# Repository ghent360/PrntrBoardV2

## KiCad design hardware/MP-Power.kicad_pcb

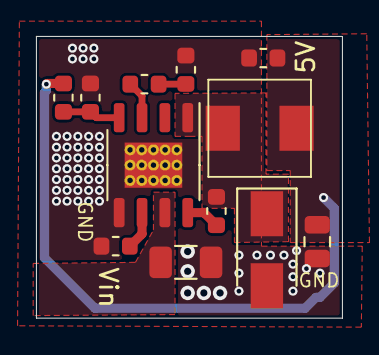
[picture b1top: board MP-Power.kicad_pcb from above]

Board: 2 copper layers, 17.0 x 15.7 mm, 12 parts (0 on the bottom side), 9 nets.

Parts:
C1: 10uF 50V; C_1206_3216Metric
C2, C5: 0.1uF; C_0603_1608Metric
C3: 150pF; C_0603_1608Metric
C4: 22uF; C_0805_2012Metric
D1: SS34; D_SMA
L1: 10uH; MWSA0503
R1, R2: 100k; R_0603_1608Metric
R3: 210k; R_0603_1608Metric
R4: 40.2k; R_0603_1608Metric
U1: MP1584EN; SOIC-8-1EP_3.9x4.9mm_P1.27mm_EP2.514x3.2mm_ThermalVias

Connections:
/5V: C4.1, C5.1, L1.2, R3.1
/Vin: C1.1, U1.7
GND: C1.2, C4.2, C5.2, D1.2, R1.2, R2.2, R4.2, U1.5, U1.9
unnamed: C2.1, D1.1, L1.1, U1.1
unnamed: C2.2, U1.8
unnamed: C3.1, U1.3
unnamed: C3.2, R2.1
unnamed: R1.1, U1.6
unnamed: R3.2, R4.1, U1.4

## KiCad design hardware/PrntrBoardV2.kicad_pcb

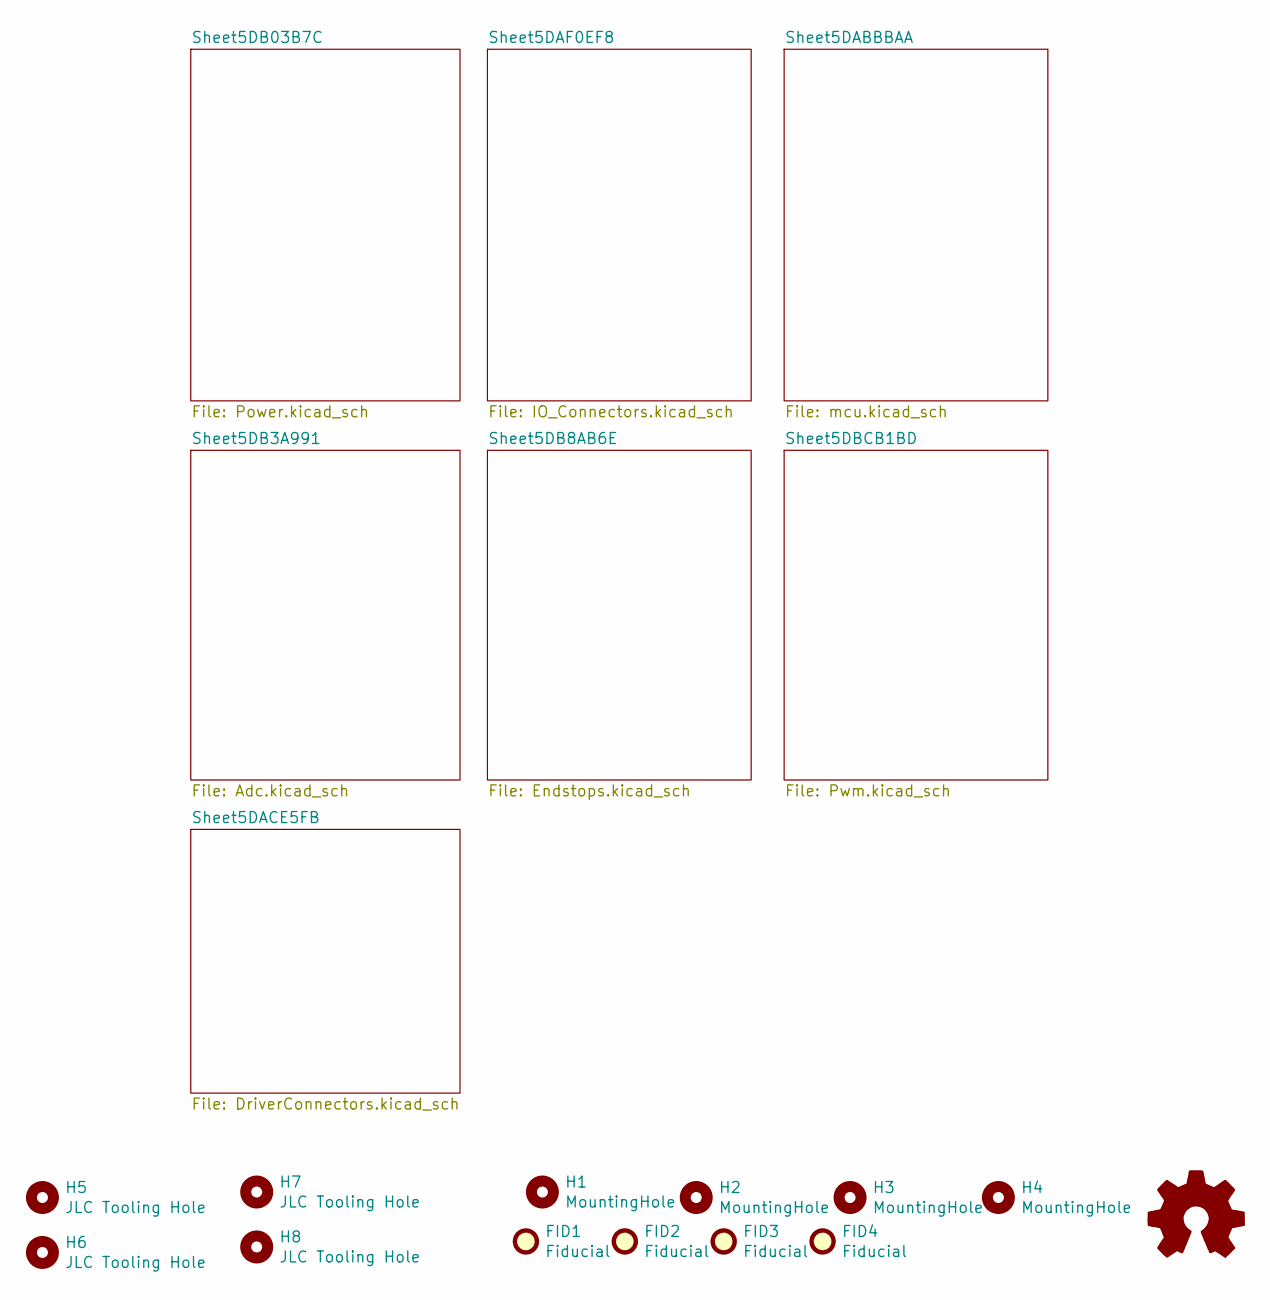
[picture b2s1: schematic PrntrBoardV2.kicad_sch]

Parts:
FID1, FID2, FID3, FID4: Fiducial; Fiducial_1mm_Dia_2.54mm_Outer_CopperTop
H1, H2, H3, H4: MountingHole; MountingHole_3.2mm_M3
H5, H6, H7, H8: JLC Tooling Hole; JLC_Tool_hole
LOGO1: Logo_Open_Hardware_Small; OSHW-Logo2_9.8x8mm_SilkScreen

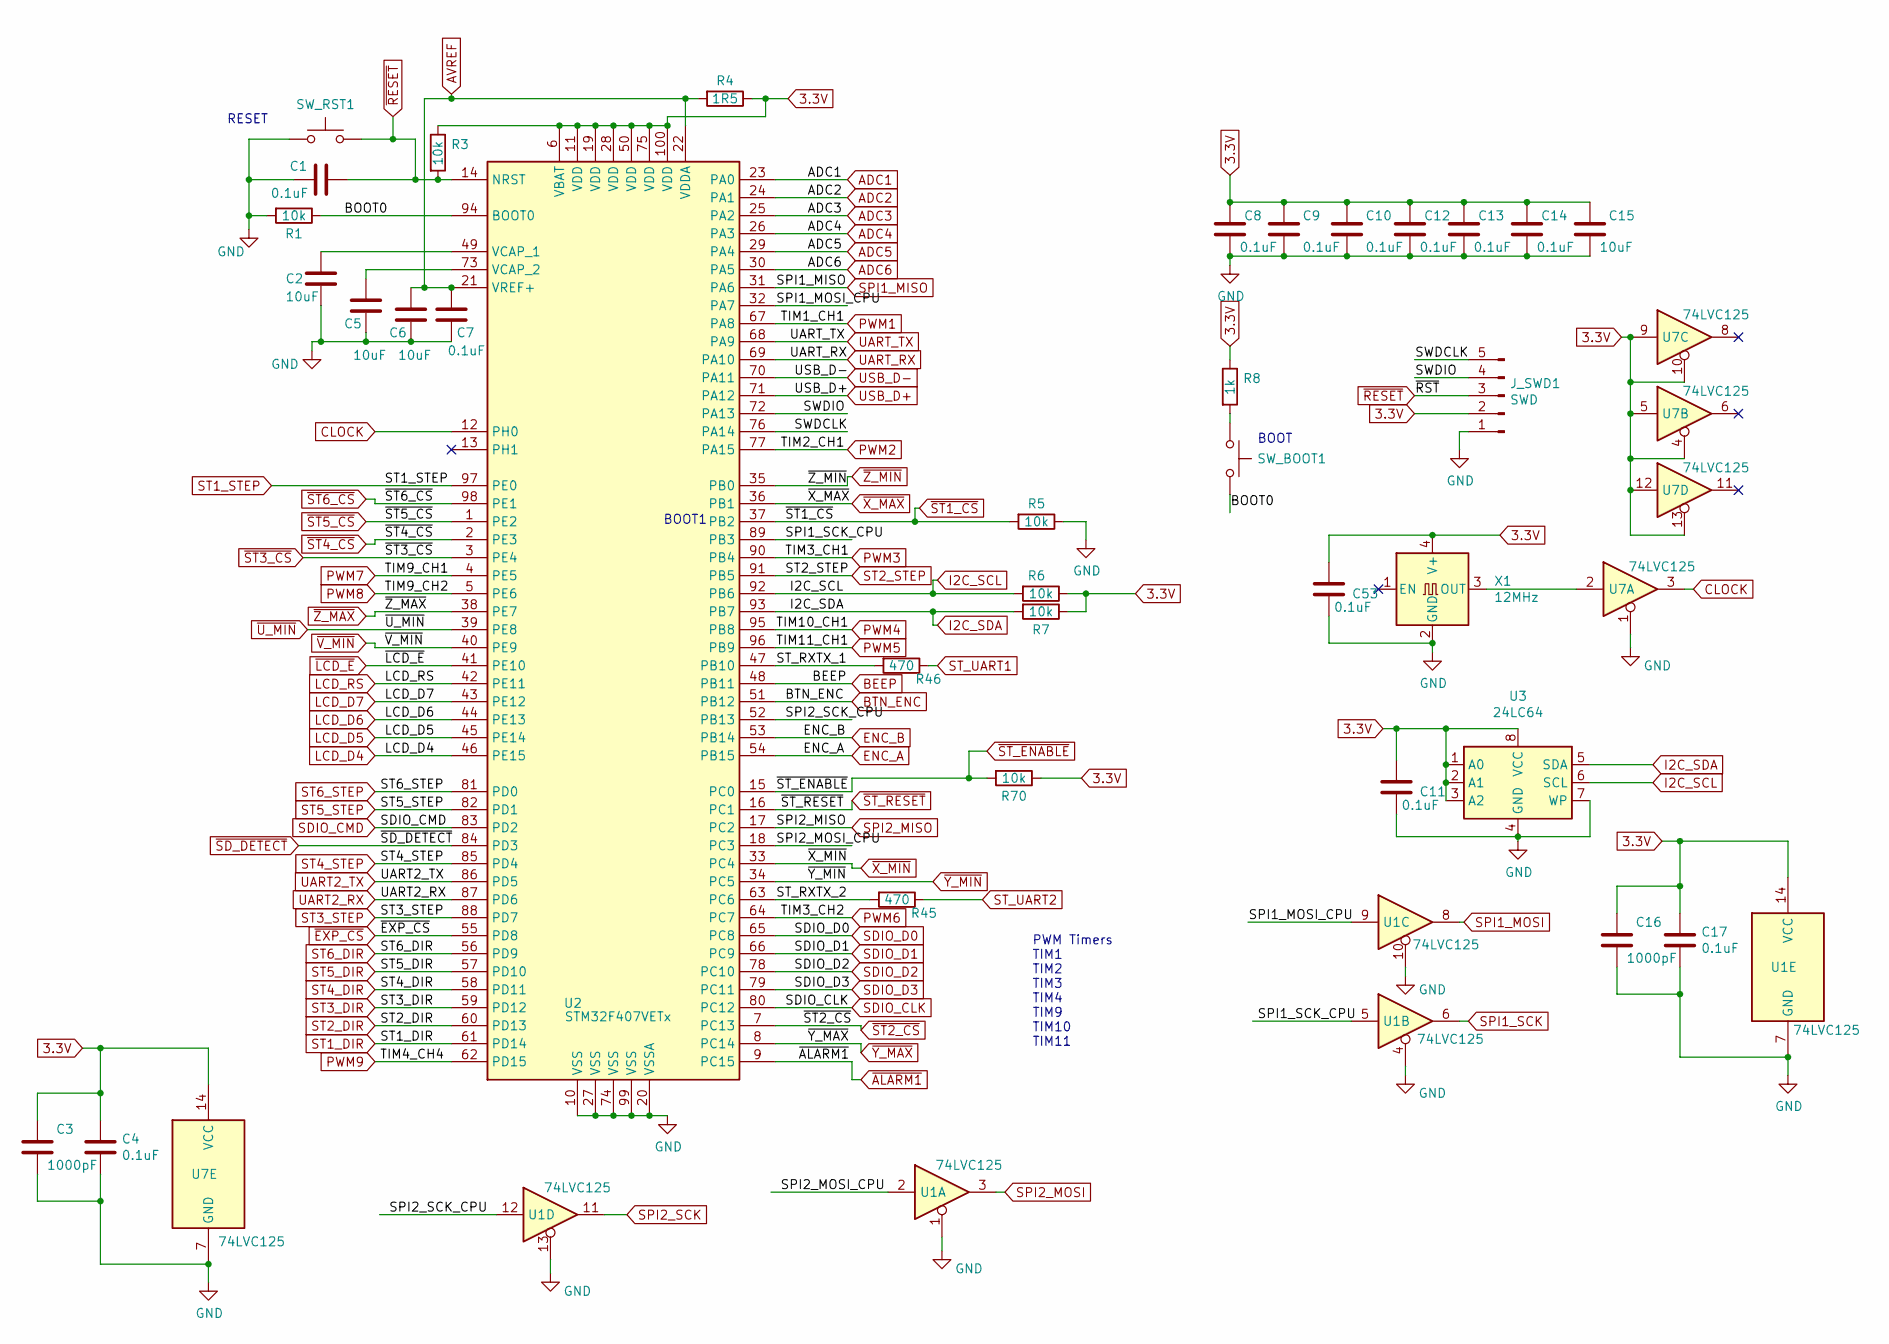
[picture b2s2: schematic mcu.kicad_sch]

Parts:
C1, C4, C7, C8, C9, C10, C11, C12, C13, C14, C17, C53: 0.1uF; C_0603_1608Metric; Part # CC0603KRX7R9BB104; LCSC Part # C14663
C2, C5, C6, C15: 10uF; C_0603_1608Metric; Part # CL10A106KP8NNNC; LCSC Part # C19702
C3, C16: 1000pF; C_0603_1608Metric; Part # CL10B102KB8NNNC; LCSC Part # C1588
J_SWD1: SWD; PinHeader_1x05_P2.54mm_Vertical
R1, R3, R5, R6, R7, R70: 10k; R_0603_1608Metric; Part # 0603WAF1002T5E; LCSC Part # C25804
R4: 1R5; R_0603_1608Metric; Part # 0603WAF220KT5E; LCSC Part # C22939
R8: 1k; R_0603_1608Metric; Part # 0603WAF1001T5E; LCSC Part # C21190
R45, R46: 470; R_0603_1608Metric; Part # 0603WAF4700T5E; LCSC Part # C23179
SW_BOOT1: SW_Push; Button_4x4; Part # TS-1187A-B-A-B; LCSC Part # C318884
SW_RST1: SW_Push; Button_4x4; Part # TS-1187A-B-A-B; LCSC Part # C318884
U1, U7: 74LVC125; TSSOP-14_4.4x5mm_P0.65mm; Part # 74LVC125APW,118; LCSC Part # C6059
U2: STM32F407VETx; LQFP-100_14x14mm_P0.5mm; Part # STM32F407VET6; LCSC Part # C28730
U3: 24LC64; SO-8_3.9x4.9mm_P1.27mm; Part # 24LC64T-I/SN; LCSC Part # C5460
X1: 12MHz; Oscillator_SMD_EuroQuartz_XO32-4Pin_3.2x2.5mm; Part# SIT1602AI-22-33E-12.000000D; LCSC Part # C29752

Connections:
3.3V: C3.1, C4.1, C8.1, C9.1, C10.1, C11.1, C12.1, C13.1, C14.1, C15.1, C16.1, C17.1, C53.1, J_SWD1.2, R3.1, R4.1, R6.1, R7.1, R8.1, R70.1, U1.14 (VCC), U2.6 (VBAT), U2.11 (VDD), U2.19 (VDD), U2.28 (VDD), U2.50 (VDD), U2.75 (VDD), U2.100 (VDD), U3.1 (A0), U3.2 (A1), U3.3 (A2), U3.8 (VCC), U7.4, U7.5, U7.9, U7.10, U7.12, U7.13, U7.14 (VCC), X1.4 (V+); also elsewhere on the board
/Sheet5DABBBAA/BOOT0: R1.1, SW_BOOT1.2, U2.94 (BOOT0)
/Sheet5DABBBAA/SPI1_MOSI_CPU: U1.9, U2.32 (PA7)
/Sheet5DABBBAA/SPI1_SCK_CPU: U1.5, U2.89 (PB3)
/Sheet5DABBBAA/SPI2_MOSI_CPU: U1.2, U2.18 (PC3)
/Sheet5DABBBAA/SPI2_SCK_CPU: U1.12, U2.52 (PB13)
/Sheet5DABBBAA/ST_RXTX_1: R46.2, U2.47 (PB10)
/Sheet5DABBBAA/ST_RXTX_2: R45.2, U2.63 (PC6)
/Sheet5DABBBAA/SWDCLK: J_SWD1.5, U2.76 (PA14)
/Sheet5DABBBAA/SWDIO: J_SWD1.4, U2.72 (PA13)
ADC1: U2.23 (PA0); also elsewhere on the board
ADC2: U2.24 (PA1); also elsewhere on the board
ADC3: U2.25 (PA2); also elsewhere on the board
ADC4: U2.26 (PA3); also elsewhere on the board
ADC5: U2.29 (PA4); also elsewhere on the board
ADC6: U2.30 (PA5); also elsewhere on the board
AVREF: C6.1, C7.1, R4.2, U2.21 (VREF+), U2.22 (VDDA); also elsewhere on the board
BEEP: U2.48 (PB11); also elsewhere on the board
BTN_ENC: U2.51 (PB12); also elsewhere on the board
CLOCK: U2.12 (PH0), U7.3; also elsewhere on the board
ENC_A: U2.54 (PB15); also elsewhere on the board
ENC_B: U2.53 (PB14); also elsewhere on the board
GND: C1.2, C2.2, C3.2, C4.2, C5.2, C6.2, C7.2, C8.2, C9.2, C10.2, C11.2, C12.2, C13.2, C14.2, C15.2, C16.2, C17.2, C53.2, J_SWD1.1, R1.2, R5.1, SW_RST1.1, U1.1, U1.4, U1.7 (GND), U1.10, U1.13, U2.10 (VSS), U2.20 (VSSA), U2.27 (VSS), U2.74 (VSS), U2.99 (VSS), U3.4 (GND), U3.7 (WP), U7.1, U7.7 (GND), X1.2 (GND); also elsewhere on the board
I2C_SCL: R6.2, U2.92 (PB6), U3.6 (SCL); also elsewhere on the board
I2C_SDA: R7.2, U2.93 (PB7), U3.5 (SDA); also elsewhere on the board
LCD_D4: U2.46 (PE15); also elsewhere on the board
LCD_D5: U2.45 (PE14); also elsewhere on the board
LCD_D6: U2.44 (PE13); also elsewhere on the board
LCD_D7: U2.43 (PE12); also elsewhere on the board
LCD_RS: U2.42 (PE11); also elsewhere on the board
unnamed: C2.1, U2.49 (VCAP_1)
unnamed: C5.1, U2.73 (VCAP_2)
unnamed: R8.2, SW_BOOT1.1
unnamed: U7.2, X1.3 (OUT)
PWM1: U2.67 (PA8); also elsewhere on the board
PWM2: U2.77 (PA15); also elsewhere on the board
PWM3: U2.90 (PB4); also elsewhere on the board
PWM4: U2.95 (PB8); also elsewhere on the board
PWM5: U2.96 (PB9); also elsewhere on the board
PWM6: U2.64 (PC7); also elsewhere on the board
PWM7: U2.4 (PE5); also elsewhere on the board
PWM8: U2.5 (PE6); also elsewhere on the board
PWM9: U2.62 (PD15); also elsewhere on the board
SDIO_CLK: U2.80 (PC12); also elsewhere on the board
SDIO_CMD: U2.83 (PD2); also elsewhere on the board
SDIO_D0: U2.65 (PC8); also elsewhere on the board
SDIO_D1: U2.66 (PC9); also elsewhere on the board
SDIO_D2: U2.78 (PC10); also elsewhere on the board
SDIO_D3: U2.79 (PC11); also elsewhere on the board
SPI1_MISO: U2.31 (PA6); also elsewhere on the board
SPI1_MOSI: U1.8; also elsewhere on the board
SPI1_SCK: U1.6; also elsewhere on the board
SPI2_MISO: U2.17 (PC2); also elsewhere on the board
SPI2_MOSI: U1.3; also elsewhere on the board
SPI2_SCK: U1.11; also elsewhere on the board
ST1_DIR: U2.61 (PD14); also elsewhere on the board
ST1_STEP: U2.97 (PE0); also elsewhere on the board
ST2_DIR: U2.60 (PD13); also elsewhere on the board
ST2_STEP: U2.91 (PB5); also elsewhere on the board
ST3_DIR: U2.59 (PD12); also elsewhere on the board
ST3_STEP: U2.88 (PD7); also elsewhere on the board
ST4_DIR: U2.58 (PD11); also elsewhere on the board
ST4_STEP: U2.85 (PD4); also elsewhere on the board
ST5_DIR: U2.57 (PD10); also elsewhere on the board
ST5_STEP: U2.82 (PD1); also elsewhere on the board
ST6_DIR: U2.56 (PD9); also elsewhere on the board
ST6_STEP: U2.81 (PD0); also elsewhere on the board
ST_UART1: R46.1; also elsewhere on the board
ST_UART2: R45.1; also elsewhere on the board
UART2_RX: U2.87 (PD6); also elsewhere on the board
UART2_TX: U2.86 (PD5); also elsewhere on the board
UART_RX: U2.69 (PA10); also elsewhere on the board
UART_TX: U2.68 (PA9); also elsewhere on the board
USB_D+: U2.71 (PA12); also elsewhere on the board
USB_D-: U2.70 (PA11); also elsewhere on the board
~ALARM1: U2.9 (PC15); also elsewhere on the board
~EXP_CS: U2.55 (PD8); also elsewhere on the board
~LCD_E: U2.41 (PE10); also elsewhere on the board
~RESET: C1.1, J_SWD1.3, R3.2, SW_RST1.2, U2.14 (NRST); also elsewhere on the board
~SD_DETECT: U2.84 (PD3); also elsewhere on the board
~ST1_CS: R5.2, U2.37 (PB2); also elsewhere on the board
~ST2_CS: U2.7 (PC13); also elsewhere on the board
~ST3_CS: U2.3 (PE4); also elsewhere on the board
~ST4_CS: U2.2 (PE3); also elsewhere on the board
~ST5_CS: U2.1 (PE2); also elsewhere on the board
~ST6_CS: U2.98 (PE1); also elsewhere on the board
~ST_ENABLE: R70.2, U2.15 (PC0); also elsewhere on the board
~ST_RESET: U2.16 (PC1); also elsewhere on the board
~U_MIN: U2.39 (PE8); also elsewhere on the board
~V_MIN: U2.40 (PE9); also elsewhere on the board
~X_MAX: U2.36 (PB1); also elsewhere on the board
~X_MIN: U2.33 (PC4); also elsewhere on the board
~Y_MAX: U2.8 (PC14); also elsewhere on the board
~Y_MIN: U2.34 (PC5); also elsewhere on the board
~Z_MAX: U2.38 (PE7); also elsewhere on the board
~Z_MIN: U2.35 (PB0); also elsewhere on the board

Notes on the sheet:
RESET
BOOT1
PWM Timers TIM1 TIM2 TIM3 TIM4 TIM9 TIM10 TIM11
BOOT

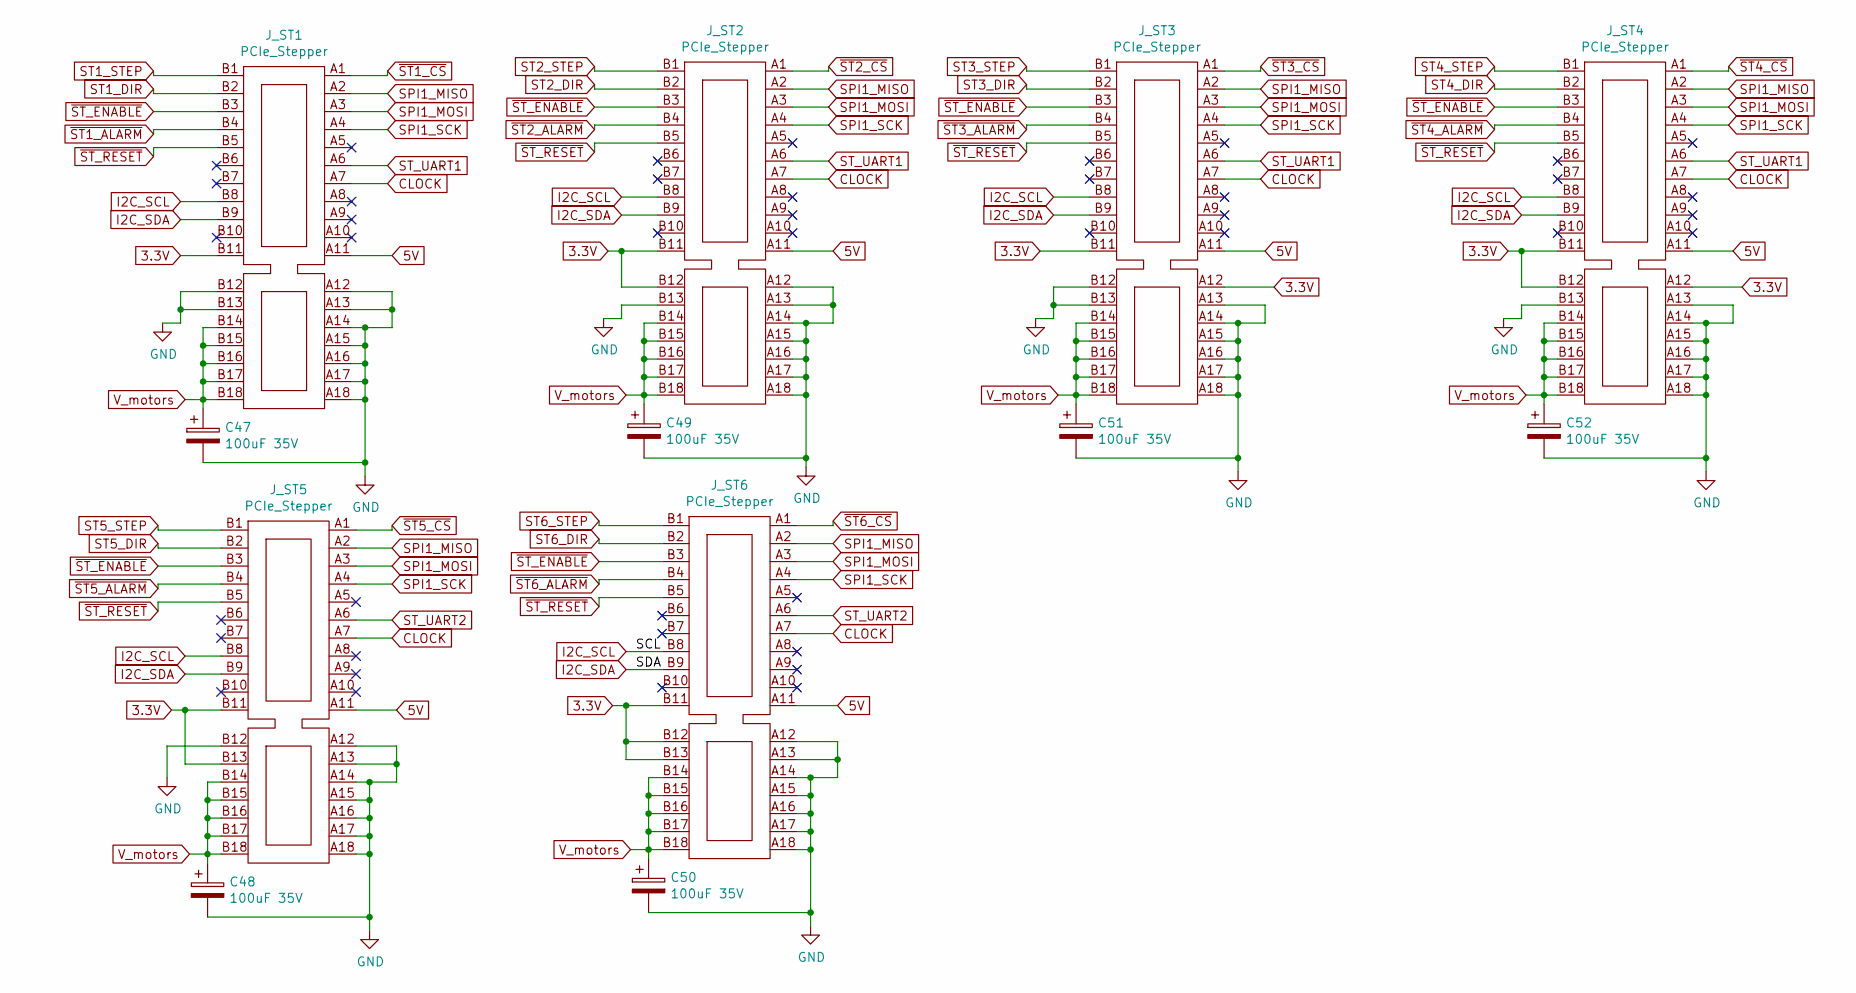
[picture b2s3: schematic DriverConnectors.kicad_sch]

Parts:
C47, C48, C49, C50, C51, C52: 100uF 35V; CP_Elec_6.3x7.7; Part # VES101M1VTR-0607; LCSC Part # C134792
J_ST1, J_ST2, J_ST3, J_ST4, J_ST5, J_ST6: PCIe_Stepper; AMPHENOL_10018784-10210TLF

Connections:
3.3V: J_ST1.B11, J_ST2.B11, J_ST2.B12, J_ST3.A12, J_ST3.B11, J_ST4.A12, J_ST4.B11, J_ST4.B12, J_ST5.B11, J_ST5.B13, J_ST6.B11, J_ST6.B12, J_ST6.B13; also elsewhere on the board
5V: J_ST1.A11, J_ST2.A11, J_ST3.A11, J_ST4.A11, J_ST5.A11, J_ST6.A11; also elsewhere on the board
CLOCK: J_ST1.A7, J_ST2.A7, J_ST3.A7, J_ST4.A7, J_ST5.A7, J_ST6.A7; also elsewhere on the board
GND: C47.2, C48.2, C49.2, C50.2, C51.2, C52.2, J_ST1.A12, J_ST1.A13, J_ST1.A14, J_ST1.A15, J_ST1.A16, J_ST1.A17, J_ST1.A18, J_ST1.B12, J_ST1.B13, J_ST2.A12, J_ST2.A13, J_ST2.A14, J_ST2.A15, J_ST2.A16, J_ST2.A17, J_ST2.A18, J_ST2.B13, J_ST3.A13, J_ST3.A14, J_ST3.A15, J_ST3.A16, J_ST3.A17, J_ST3.A18, J_ST3.B12, J_ST3.B13, J_ST4.A13, J_ST4.A14, J_ST4.A15, J_ST4.A16, J_ST4.A17, J_ST4.A18, J_ST4.B13, J_ST5.A12, J_ST5.A13, J_ST5.A14, J_ST5.A15, J_ST5.A16, J_ST5.A17, J_ST5.A18, J_ST5.B12, J_ST6.A12, J_ST6.A13, J_ST6.A14, J_ST6.A15, J_ST6.A16, J_ST6.A17, J_ST6.A18; also elsewhere on the board
I2C_SCL: J_ST1.B8, J_ST2.B8, J_ST3.B8, J_ST4.B8, J_ST5.B8, J_ST6.B8; also elsewhere on the board
I2C_SDA: J_ST1.B9, J_ST2.B9, J_ST3.B9, J_ST4.B9, J_ST5.B9, J_ST6.B9; also elsewhere on the board
SPI1_MISO: J_ST1.A2, J_ST2.A2, J_ST3.A2, J_ST4.A2, J_ST5.A2, J_ST6.A2; also elsewhere on the board
SPI1_MOSI: J_ST1.A3, J_ST2.A3, J_ST3.A3, J_ST4.A3, J_ST5.A3, J_ST6.A3; also elsewhere on the board
SPI1_SCK: J_ST1.A4, J_ST2.A4, J_ST3.A4, J_ST4.A4, J_ST5.A4, J_ST6.A4; also elsewhere on the board
ST1_DIR: J_ST1.B2; also elsewhere on the board
ST1_STEP: J_ST1.B1; also elsewhere on the board
ST2_DIR: J_ST2.B2; also elsewhere on the board
ST2_STEP: J_ST2.B1; also elsewhere on the board
ST3_DIR: J_ST3.B2; also elsewhere on the board
ST3_STEP: J_ST3.B1; also elsewhere on the board
ST4_DIR: J_ST4.B2; also elsewhere on the board
ST4_STEP: J_ST4.B1; also elsewhere on the board
ST5_DIR: J_ST5.B2; also elsewhere on the board
ST5_STEP: J_ST5.B1; also elsewhere on the board
ST6_DIR: J_ST6.B2; also elsewhere on the board
ST6_STEP: J_ST6.B1; also elsewhere on the board
ST_UART1: J_ST1.A6, J_ST2.A6, J_ST3.A6, J_ST4.A6; also elsewhere on the board
ST_UART2: J_ST5.A6, J_ST6.A6; also elsewhere on the board
V_motors: C47.1, C48.1, C49.1, C50.1, C51.1, C52.1, J_ST1.B14, J_ST1.B15, J_ST1.B16, J_ST1.B17, J_ST1.B18, J_ST2.B14, J_ST2.B15, J_ST2.B16, J_ST2.B17, J_ST2.B18, J_ST3.B14, J_ST3.B15, J_ST3.B16, J_ST3.B17, J_ST3.B18, J_ST4.B14, J_ST4.B15, J_ST4.B16, J_ST4.B17, J_ST4.B18, J_ST5.B14, J_ST5.B15, J_ST5.B16, J_ST5.B17, J_ST5.B18, J_ST6.B14, J_ST6.B15, J_ST6.B16, J_ST6.B17, J_ST6.B18; also elsewhere on the board
~ST1_ALARM: J_ST1.B4; also elsewhere on the board
~ST1_CS: J_ST1.A1; also elsewhere on the board
~ST2_ALARM: J_ST2.B4; also elsewhere on the board
~ST2_CS: J_ST2.A1; also elsewhere on the board
~ST3_ALARM: J_ST3.B4; also elsewhere on the board
~ST3_CS: J_ST3.A1; also elsewhere on the board
~ST4_ALARM: J_ST4.B4; also elsewhere on the board
~ST4_CS: J_ST4.A1; also elsewhere on the board
~ST5_ALARM: J_ST5.B4; also elsewhere on the board
~ST5_CS: J_ST5.A1; also elsewhere on the board
~ST6_ALARM: J_ST6.B4; also elsewhere on the board
~ST6_CS: J_ST6.A1; also elsewhere on the board
~ST_ENABLE: J_ST1.B3, J_ST2.B3, J_ST3.B3, J_ST4.B3, J_ST5.B3, J_ST6.B3; also elsewhere on the board
~ST_RESET: J_ST1.B5, J_ST2.B5, J_ST3.B5, J_ST4.B5, J_ST5.B5, J_ST6.B5; also elsewhere on the board

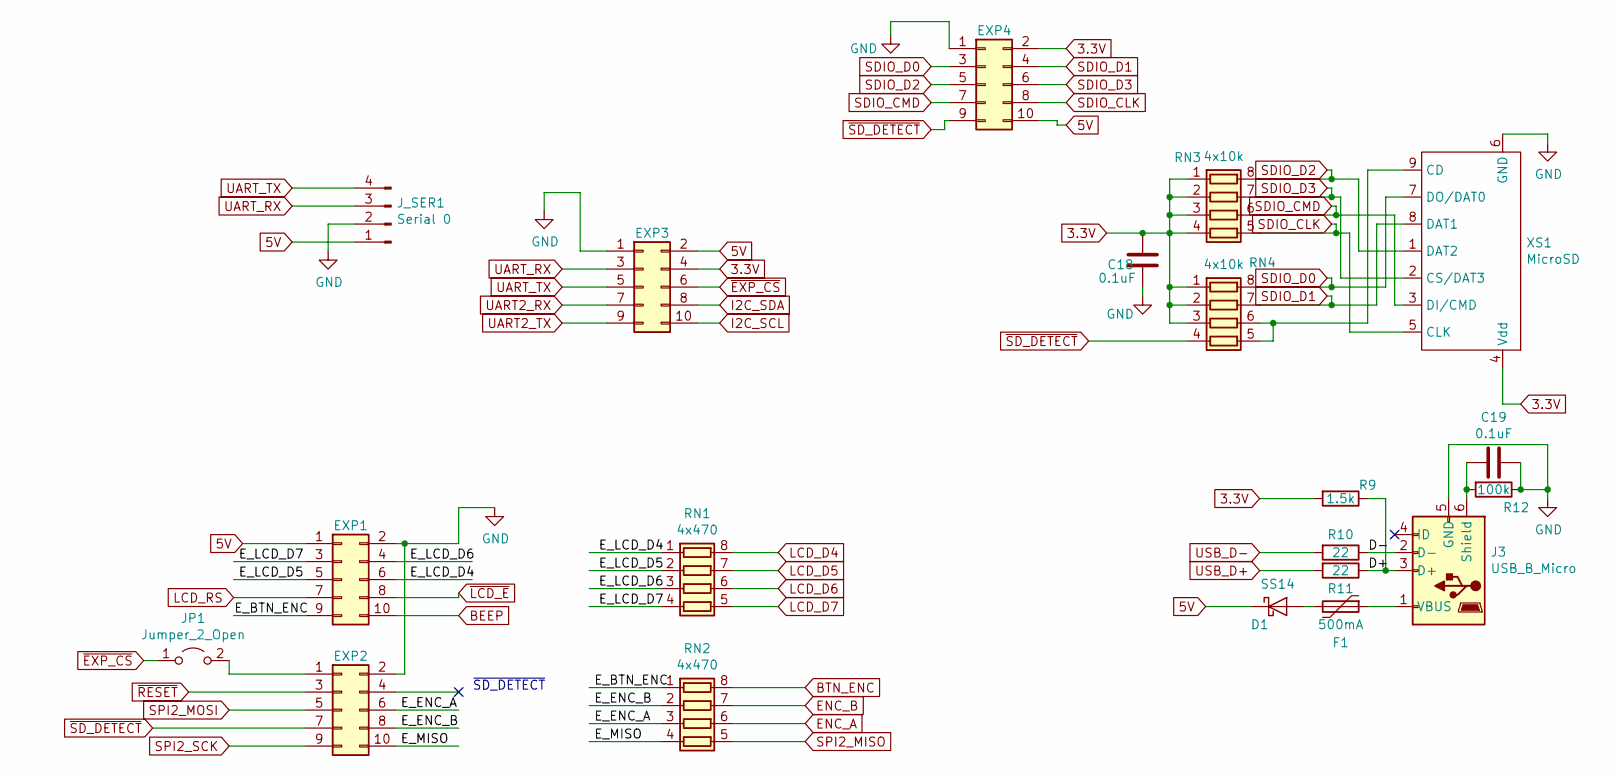
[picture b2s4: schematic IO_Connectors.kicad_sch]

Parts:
C18, C19: 0.1uF; C_0603_1608Metric; Part # CC0603KRX7R9BB104; LCSC Part # C14663
D1: SS14; D_SMA; Part # SS14; LCSC Part # C2480
EXP1, EXP2, EXP3, EXP4: IDC 2x5; IDC-Header_2x05_P2.54mm_Vertical; LCSC Part # C5661
F1: 500mA; R_0603_1608Metric; Part # TLC-FSMD050; LCSC Part # C261937
J3: USB_B_Micro; MC-101C; Part # SOFNG MC-101C; LCSC Part # C183609
JP1: Jumper_2_Open; PinHeader_1x02_P2.54mm_Vertical; LCSC Part # C160332
J_SER1: Serial 0; PinHeader_1x04_P2.54mm_Vertical; LCSC Part # C358686
R9: 1.5k; R_0603_1608Metric; Part # 0603WAF1501T5E; LCSC Part # C22843
R10, R11: 22; R_0603_1608Metric; Part # 0603WAF220JT5E; LCSC Part # C23345
R12: 100k; R_0603_1608Metric; Part # 0603WAF1003T5E; LCSC Part # C25803
RN1, RN2: 4x470; R_Array_Convex_4x0603; Part # 4D03WGJ0471T5E; LCSC Part # C25510
RN3, RN4: 4x10k; R_Array_Convex_4x0603; Part # 4D03WGJ0103T5E; LCSC Part # C29718
XS1: MicroSD; Conn_uSDcard; Part # SOFNG TF-15×15; LCSC Part # C111196

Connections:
3.3V: C18.1, EXP3.4, EXP4.2, R9.2, RN3.1 (R1.1), RN3.2 (R2.1), RN3.3 (R3.1), RN3.4 (R4.1), RN4.1 (R1.1), RN4.2 (R2.1), RN4.3 (R3.1), XS1.4 (Vdd); also elsewhere on the board
5V: D1.1 (K), EXP1.1, EXP3.2, EXP4.10, J_SER1.1; also elsewhere on the board
/Sheet5DAF0EF8/D+: J3.3 (D+), R9.1, R11.1
/Sheet5DAF0EF8/D-: J3.2 (D-), R10.1
/Sheet5DAF0EF8/E_BTN_ENC: EXP1.9, RN2.1 (R1.1)
/Sheet5DAF0EF8/E_ENC_A: EXP2.6, RN2.3 (R3.1)
/Sheet5DAF0EF8/E_ENC_B: EXP2.8, RN2.2 (R2.1)
/Sheet5DAF0EF8/E_LCD_D4: EXP1.6, RN1.1 (R1.1)
/Sheet5DAF0EF8/E_LCD_D5: EXP1.5, RN1.2 (R2.1)
/Sheet5DAF0EF8/E_LCD_D6: EXP1.4, RN1.3 (R3.1)
/Sheet5DAF0EF8/E_LCD_D7: EXP1.3, RN1.4 (R4.1)
/Sheet5DAF0EF8/E_MISO: EXP2.10, RN2.4 (R4.1)
BEEP: EXP1.10; also elsewhere on the board
BTN_ENC: RN2.8 (R1.2); also elsewhere on the board
ENC_A: RN2.6 (R3.2); also elsewhere on the board
ENC_B: RN2.7 (R2.2); also elsewhere on the board
GND: C18.2, C19.1, EXP1.2, EXP2.2, EXP3.1, EXP4.1, J3.5 (GND), J_SER1.2, R12.1, XS1.6 (GND); also elsewhere on the board
I2C_SCL: EXP3.10; also elsewhere on the board
I2C_SDA: EXP3.8; also elsewhere on the board
LCD_D4: RN1.8 (R1.2); also elsewhere on the board
LCD_D5: RN1.7 (R2.2); also elsewhere on the board
LCD_D6: RN1.6 (R3.2); also elsewhere on the board
LCD_D7: RN1.5 (R4.2); also elsewhere on the board
LCD_RS: EXP1.7; also elsewhere on the board
unnamed: C19.2, J3.6 (Shield), R12.2
unnamed: D1.2 (A), F1.2
unnamed: EXP2.1, JP1.2 (B)
unnamed: F1.1, J3.1 (VBUS)
unnamed: RN4.5 (R4.2), RN4.6 (R3.2), XS1.9 (CD)
SDIO_CLK: EXP4.8, RN3.5 (R4.2), XS1.5 (CLK); also elsewhere on the board
SDIO_CMD: EXP4.7, RN3.6 (R3.2), XS1.3 (DI/CMD); also elsewhere on the board
SDIO_D0: EXP4.3, RN4.8 (R1.2), XS1.7 (DO/DAT0); also elsewhere on the board
SDIO_D1: EXP4.4, RN4.7 (R2.2), XS1.8 (DAT1); also elsewhere on the board
SDIO_D2: EXP4.5, RN3.8 (R1.2), XS1.1 (DAT2); also elsewhere on the board
SDIO_D3: EXP4.6, RN3.7 (R2.2), XS1.2 (CS/DAT3); also elsewhere on the board
SPI2_MISO: RN2.5 (R4.2); also elsewhere on the board
SPI2_MOSI: EXP2.5; also elsewhere on the board
SPI2_SCK: EXP2.9; also elsewhere on the board
UART2_RX: EXP3.7; also elsewhere on the board
UART2_TX: EXP3.9; also elsewhere on the board
UART_RX: EXP3.3, J_SER1.3; also elsewhere on the board
UART_TX: EXP3.5, J_SER1.4; also elsewhere on the board
USB_D+: R11.2; also elsewhere on the board
USB_D-: R10.2; also elsewhere on the board
~EXP_CS: EXP3.6, JP1.1 (A); also elsewhere on the board
~LCD_E: EXP1.8; also elsewhere on the board
~RESET: EXP2.3; also elsewhere on the board
~SD_DETECT: EXP2.7, EXP4.9, RN4.4 (R4.1); also elsewhere on the board

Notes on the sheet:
~SD_DETECT

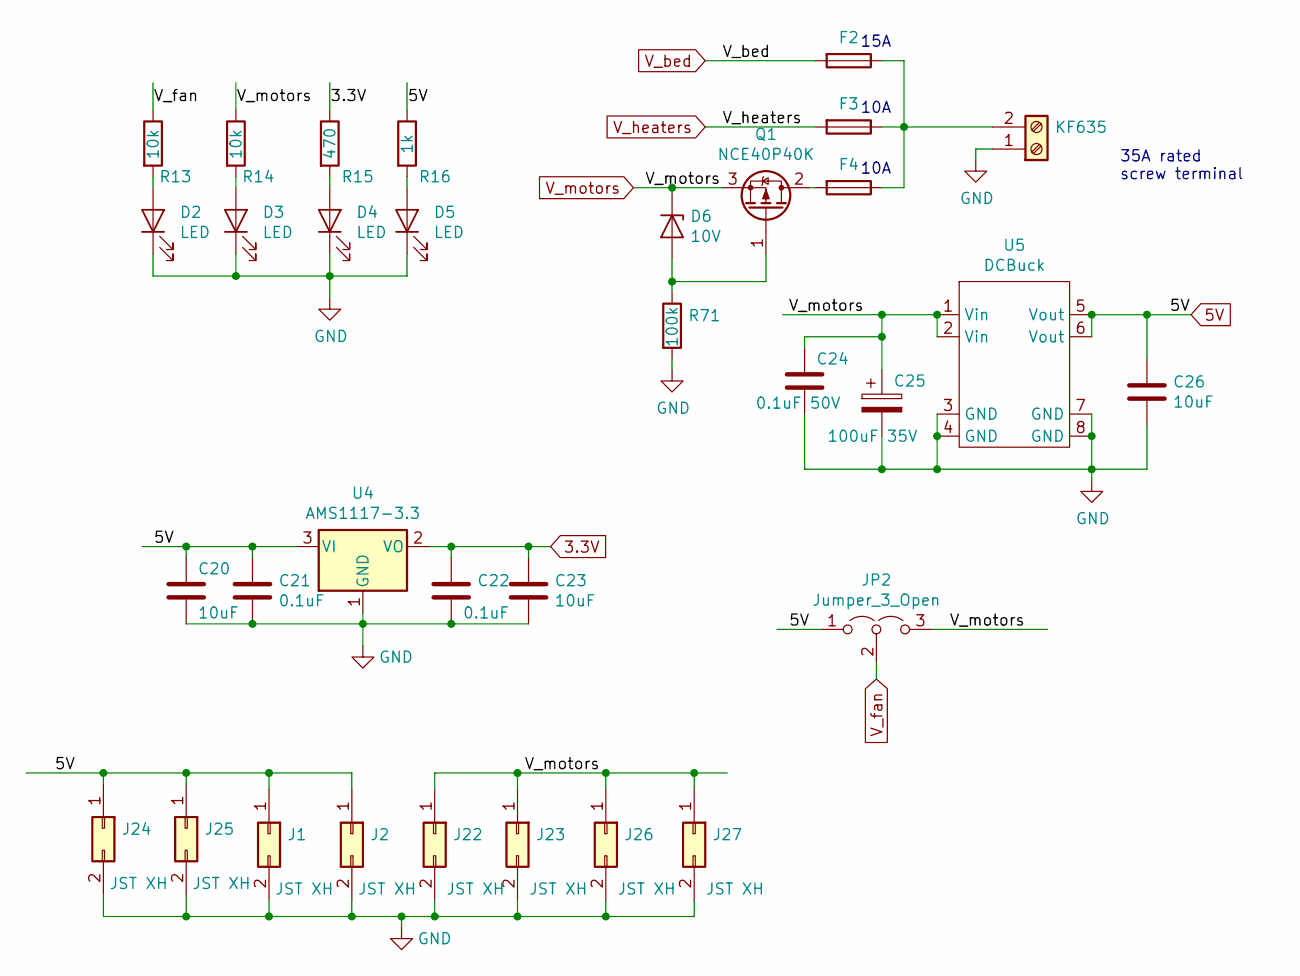
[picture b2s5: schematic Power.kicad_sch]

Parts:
C20, C23, C26: 10uF; C_0603_1608Metric; Part # CL10A106KP8NNNC; LCSC Part # C19702
C21, C22: 0.1uF; C_0603_1608Metric; Part # CC0603KRX7R9BB104; LCSC Part # C14663
C24: 0.1uF 50V; C_0603_1608Metric; Part # CL05B104KO5NNNCC0603KRX7R9BB104C; LCSC Part # C14663
C25: 100uF 35V; CP_Elec_6.3x7.7; Part # VES101M1VTR-0607; LCSC Part # C134792
D2, D3, D4, D5: LED; LED_0603_1608Metric; Part # KT-0603R; LCSC Part # C2286
D6: 10V; D_SOD-323; Part # LM3Z10VT1G; LCSC Part # C131828
F2, F3, F4: Fuse; 2410_FuseFolder
J1, J2, J22, J23, J24, J25, J26, J27: JST XH; JST_XH_B2B-XH-A_1x02_P2.50mm_Vertical
JP2: Jumper_3_Open; PinHeader_1x03_P2.54mm_Vertical; LCSC Part # C152153
J_power_in1: KF635; TerminalBlock_MetzConnect_Type701_RT11L02HGLU_1x02_P6.35mm_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
Q1: NCE40P40K; TO-252-2; Part # NCE40P40K; LCSC Part # C130100
R13, R14: 10k; R_0603_1608Metric; Part # 0603WAF1002T5E; LCSC Part # C25804
R15: 470; R_0603_1608Metric; Part # 0603WAF4700T5E; LCSC Part # C23179
R16: 1k; R_0603_1608Metric; Part # 0603WAF1001T5E; LCSC Part # C21190
R71: 100k; R_0603_1608Metric; Part # 0603WAF1003T5E; LCSC Part # C25803
U4: AMS1117-3.3; SOT-223-3_TabPin2; Part # AMS1117-3.3; LCSC Part # C6186
U5: DCBuck; Buck2217

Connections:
3.3V: C22.1, C23.1, R15.1, U4.2 (VO); also elsewhere on the board
5V: C20.1, C21.1, C26.1, J1.1, J2.1, J24.1, J25.1, JP2.1 (A), R16.1, U4.3 (VI), U5.5 (Vout), U5.6 (Vout); also elsewhere on the board
GND: C20.2, C21.2, C22.2, C23.2, C24.2, C25.2, C26.2, D2.1 (K), D3.1 (K), D4.1 (K), D5.1 (K), J1.2, J2.2, J22.2, J23.2, J24.2, J25.2, J26.2, J27.2, J_power_in1.1, R71.2, U4.1 (GND), U5.3 (GND), U5.4 (GND), U5.7 (GND), U5.8 (GND); also elsewhere on the board
unnamed: D2.2 (A), R13.2
unnamed: D3.2 (A), R14.2
unnamed: D4.2 (A), R15.2
unnamed: D5.2 (A), R16.2
unnamed: D6.2 (A), Q1.1 (G), R71.1
unnamed: F2.1, F3.1, F4.1, J_power_in1.2
unnamed: F4.2, Q1.2 (D)
V_bed: F2.2; also elsewhere on the board
V_fan: JP2.2 (C), R13.1; also elsewhere on the board
V_heaters: F3.2; also elsewhere on the board
V_motors: C24.1, C25.1, D6.1 (K), J22.1, J23.1, J26.1, J27.1, JP2.3 (B), Q1.3 (S), R14.1, U5.1 (Vin), U5.2 (Vin); also elsewhere on the board

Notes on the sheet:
15A
10A
35A rated screw terminal

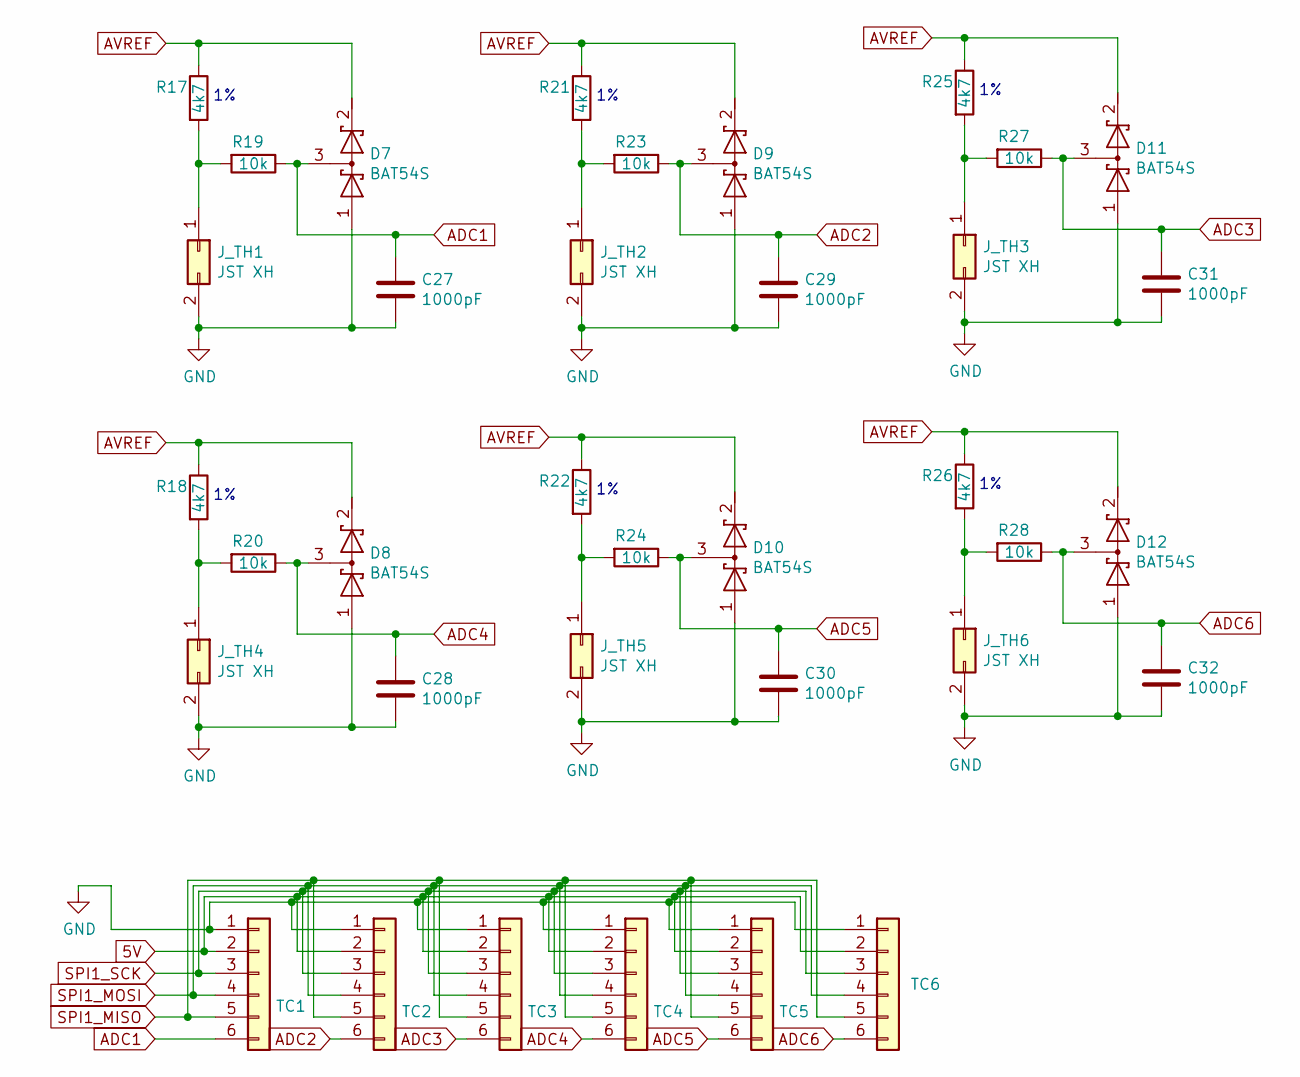
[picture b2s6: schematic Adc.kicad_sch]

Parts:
C27, C28, C29, C30, C31, C32: 1000pF; C_0603_1608Metric; Part # CL10B102KB8NNNC; LCSC Part # C1588
D7, D8, D9, D10, D11, D12: BAT54S; SOT-23; Part # BAT54S; LCSC Part # C181201
J_TH1, J_TH2, J_TH3, J_TH4, J_TH5, J_TH6: JST XH; JST_XH_B2B-XH-A_1x02_P2.50mm_Vertical
R17, R18, R21, R22, R25, R26: 4k7; R_0603_1608Metric; Part # 0603WAF4701T5E; LCSC Part # C23162
R19, R20, R23, R24, R27, R28: 10k; R_0603_1608Metric; Part # 0603WAF1002T5E; LCSC Part # C25804
TC1, TC2, TC3, TC4, TC5, TC6: TC; Molex-SL-6POS

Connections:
5V: TC1.2, TC2.2, TC3.2, TC4.2, TC5.2, TC6.2; also elsewhere on the board
ADC1: C27.1, D7.3 (common), R19.1, TC1.6; also elsewhere on the board
ADC2: C29.1, D9.3 (common), R23.1, TC2.6; also elsewhere on the board
ADC3: C31.1, D11.3 (common), R27.1, TC3.6; also elsewhere on the board
ADC4: C28.1, D8.3 (common), R20.1, TC4.6; also elsewhere on the board
ADC5: C30.1, D10.3 (common), R24.1, TC5.6; also elsewhere on the board
ADC6: C32.1, D12.3 (common), R28.1, TC6.6; also elsewhere on the board
AVREF: D7.2 (K), D8.2 (K), D9.2 (K), D10.2 (K), D11.2 (K), D12.2 (K), R17.1, R18.1, R21.1, R22.1, R25.1, R26.1; also elsewhere on the board
GND: C27.2, C28.2, C29.2, C30.2, C31.2, C32.2, D7.1 (A), D8.1 (A), D9.1 (A), D10.1 (A), D11.1 (A), D12.1 (A), J_TH1.2, J_TH2.2, J_TH3.2, J_TH4.2, J_TH5.2, J_TH6.2, TC1.1, TC2.1, TC3.1, TC4.1, TC5.1, TC6.1; also elsewhere on the board
unnamed: J_TH1.1, R17.2, R19.2
unnamed: J_TH2.1, R21.2, R23.2
unnamed: J_TH3.1, R25.2, R27.2
unnamed: J_TH4.1, R18.2, R20.2
unnamed: J_TH5.1, R22.2, R24.2
unnamed: J_TH6.1, R26.2, R28.2
SPI1_MISO: TC1.5, TC2.5, TC3.5, TC4.5, TC5.5, TC6.5; also elsewhere on the board
SPI1_MOSI: TC1.4, TC2.4, TC3.4, TC4.4, TC5.4, TC6.4; also elsewhere on the board
SPI1_SCK: TC1.3, TC2.3, TC3.3, TC4.3, TC5.3, TC6.3; also elsewhere on the board
